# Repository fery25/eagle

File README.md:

# eagle
Eagle PCB project

Pro elektrické projekty PCB desek spojené většinou s ESP či Arduino. Test.

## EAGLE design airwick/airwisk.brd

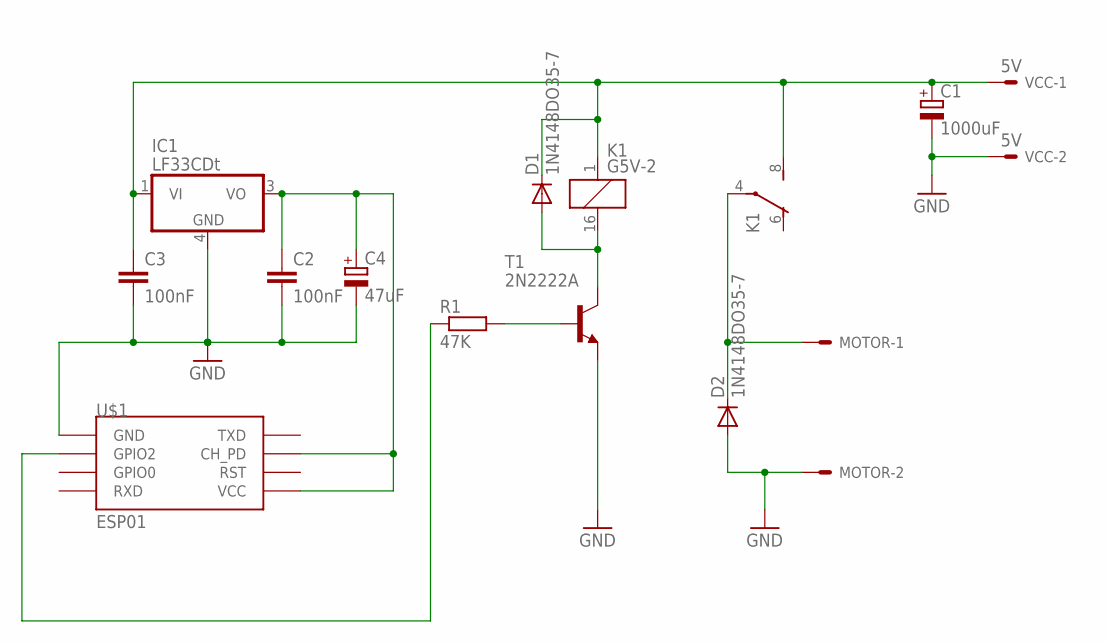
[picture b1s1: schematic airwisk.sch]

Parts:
C1: 1000uF; E3,5-8
C2, C3: 100nF; C025-025X050
C4: 47uF; E2-5
D1, D2: 1N4148DO35-7; DO35-7
IC1: LF33CDt; DPACK_3
K1: G5V-2
MOTOR: 332-02
R1: 47K; 0204/7
T1: 2N2222A; TO92
U$1: ESP01
VCC: 5V; 332-02

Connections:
GND: C1.-, C2.2, C3.2, C4.-, D2.A, IC1.4 (GND), MOTOR.2, T1.1 (E), U$1.GND, VCC.2
unnamed: C1.+, C3.1, D1.C, IC1.1 (VI), K1.1, K1.8 (S), VCC.1
unnamed: D2.C, K1.4, MOTOR.1
unnamed: R1.2, T1.2 (B)
unnamed: D1.A, K1.16 (2), T1.3 (C)
unnamed: C2.1, C4.+, IC1.3 (VO), U$1.CH_PD, U$1.VCC
unnamed: R1.1, U$1.GPIO2

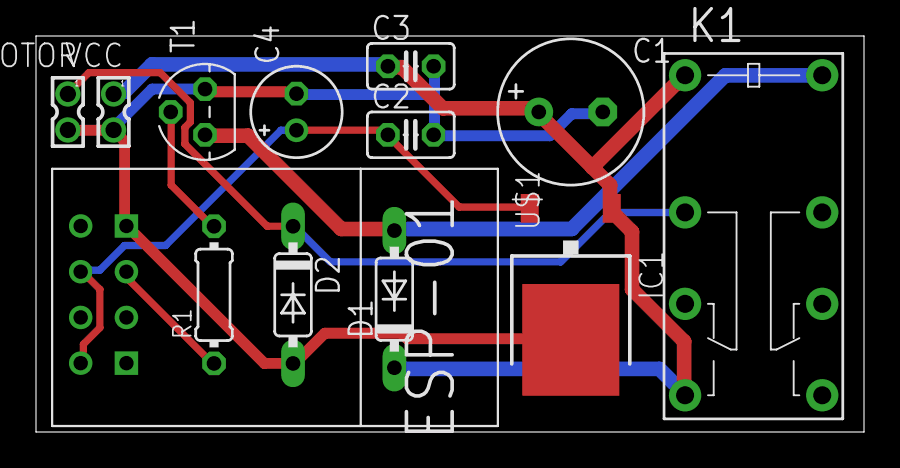
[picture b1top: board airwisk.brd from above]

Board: 2 copper layers, 46.0 x 22.0 mm, 13 parts (0 on the bottom side), 7 nets.

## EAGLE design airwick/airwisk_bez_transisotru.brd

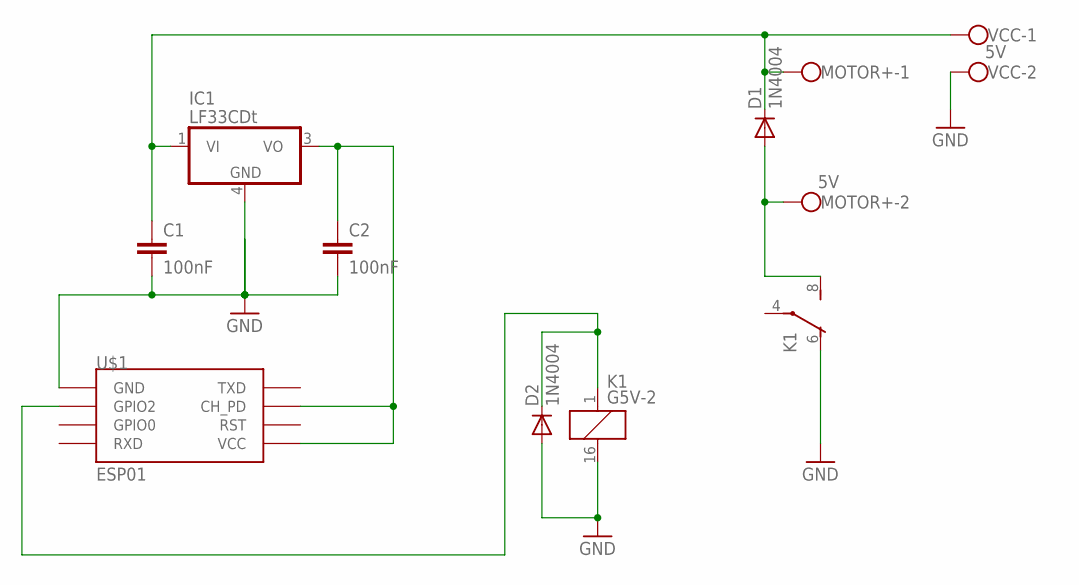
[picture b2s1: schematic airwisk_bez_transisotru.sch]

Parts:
C1, C2: 100nF; C025-025X050
D1, D2: 1N4004; DO41-10
IC1: LF33CDt; DPACK_3
K1: G5V-2
MOTOR+: 5V; W237-102
U$1: ESP01
VCC: 5V; W237-102

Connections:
GND: C1.2, C2.2, D2.A, IC1.4 (GND), K1.6 (O), K1.16 (2), U$1.GND, VCC.2
unnamed: C1.1, D1.C, IC1.1 (VI), MOTOR+.1, VCC.1
unnamed: D1.A, K1.8 (S), MOTOR+.2
unnamed: D2.C, K1.1, U$1.GPIO2
unnamed: C2.1, IC1.3 (VO), U$1.CH_PD, U$1.VCC

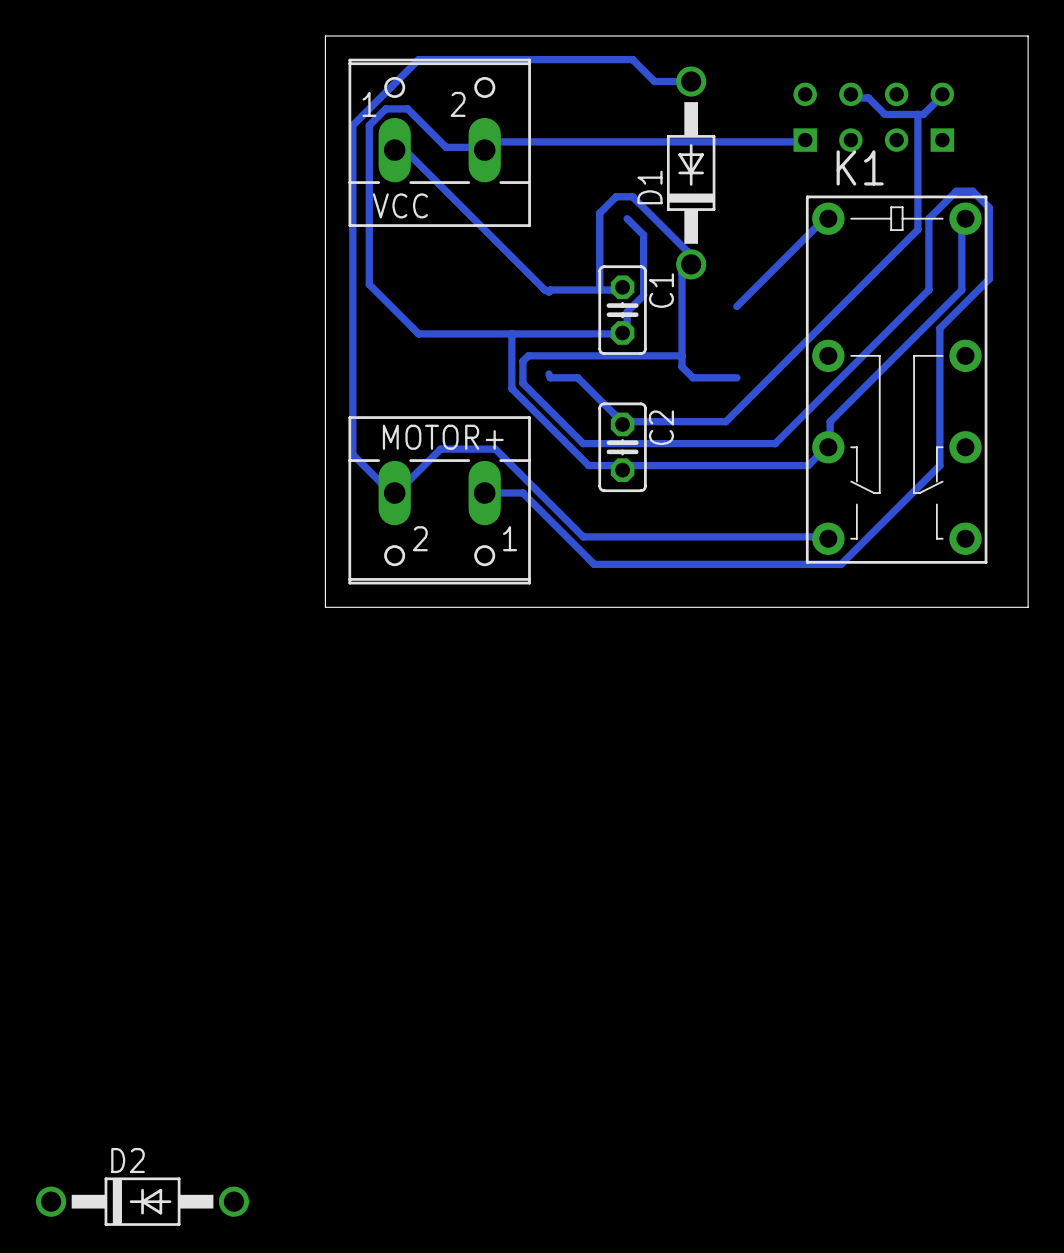
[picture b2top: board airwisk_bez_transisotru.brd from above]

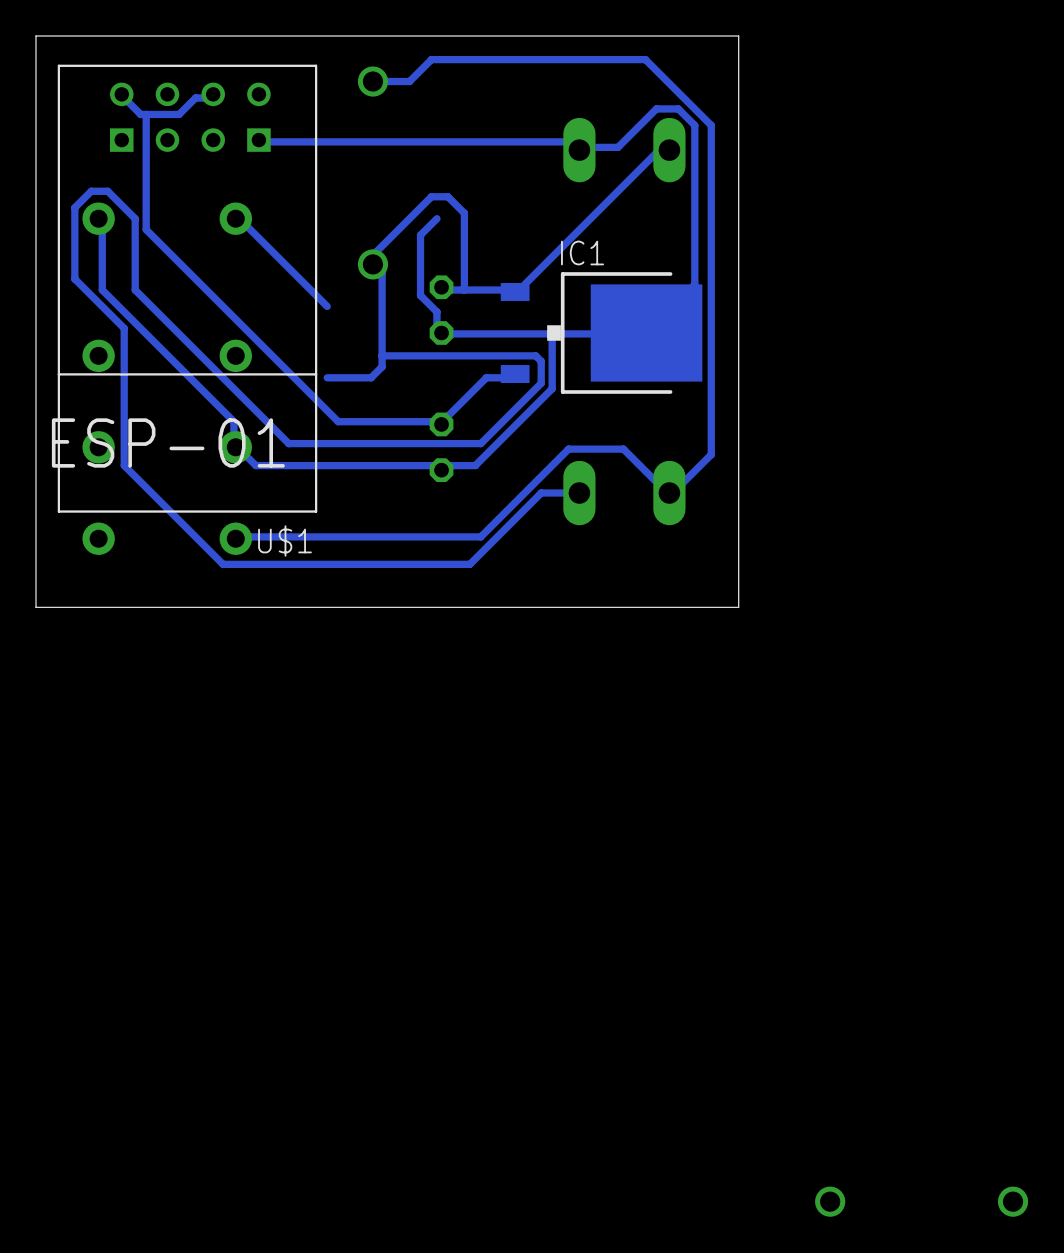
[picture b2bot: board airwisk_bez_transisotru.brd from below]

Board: 2 copper layers, 39.0 x 31.7 mm, 10 parts (2 on the bottom side), 5 nets.

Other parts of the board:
DRILEGEND: DRILEGEND

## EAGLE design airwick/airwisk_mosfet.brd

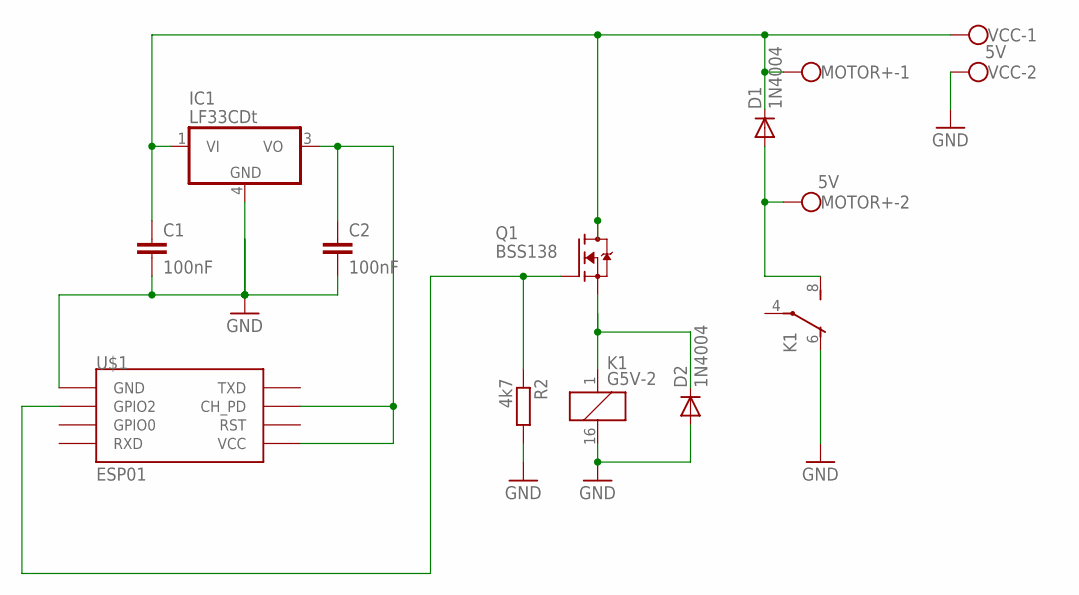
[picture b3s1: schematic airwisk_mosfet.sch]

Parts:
C1, C2: 100nF; C025-025X050
D1, D2: 1N4004; DO41-10
IC1: LF33CDt; DPACK_3
K1: G5V-2
MOTOR+: 5V; W237-102
Q1: BSS138; SOT23
R2: 4k7; 0204/7
U$1: ESP01
VCC: 5V; W237-102

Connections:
GND: C1.2, C2.2, D2.A, IC1.4 (GND), K1.6 (O), K1.16 (2), R2.2, U$1.GND, VCC.2
unnamed: C1.1, D1.C, IC1.1 (VI), MOTOR+.1, Q1.3 (D), VCC.1
unnamed: D1.A, K1.8 (S), MOTOR+.2
unnamed: Q1.1 (G), R2.1, U$1.GPIO2
unnamed: D2.C, K1.1, Q1.2 (S)
unnamed: C2.1, IC1.3 (VO), U$1.CH_PD, U$1.VCC

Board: 2 copper layers, 11 parts (3 on the bottom side), 6 nets, no tracks yet.

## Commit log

2017-01-18 First Commint
2017-01-18 Přidání většího popisku.
2017-01-18 Test
2017-01-26 update R1 to 47k and delete R2 => for GPO02 to low
